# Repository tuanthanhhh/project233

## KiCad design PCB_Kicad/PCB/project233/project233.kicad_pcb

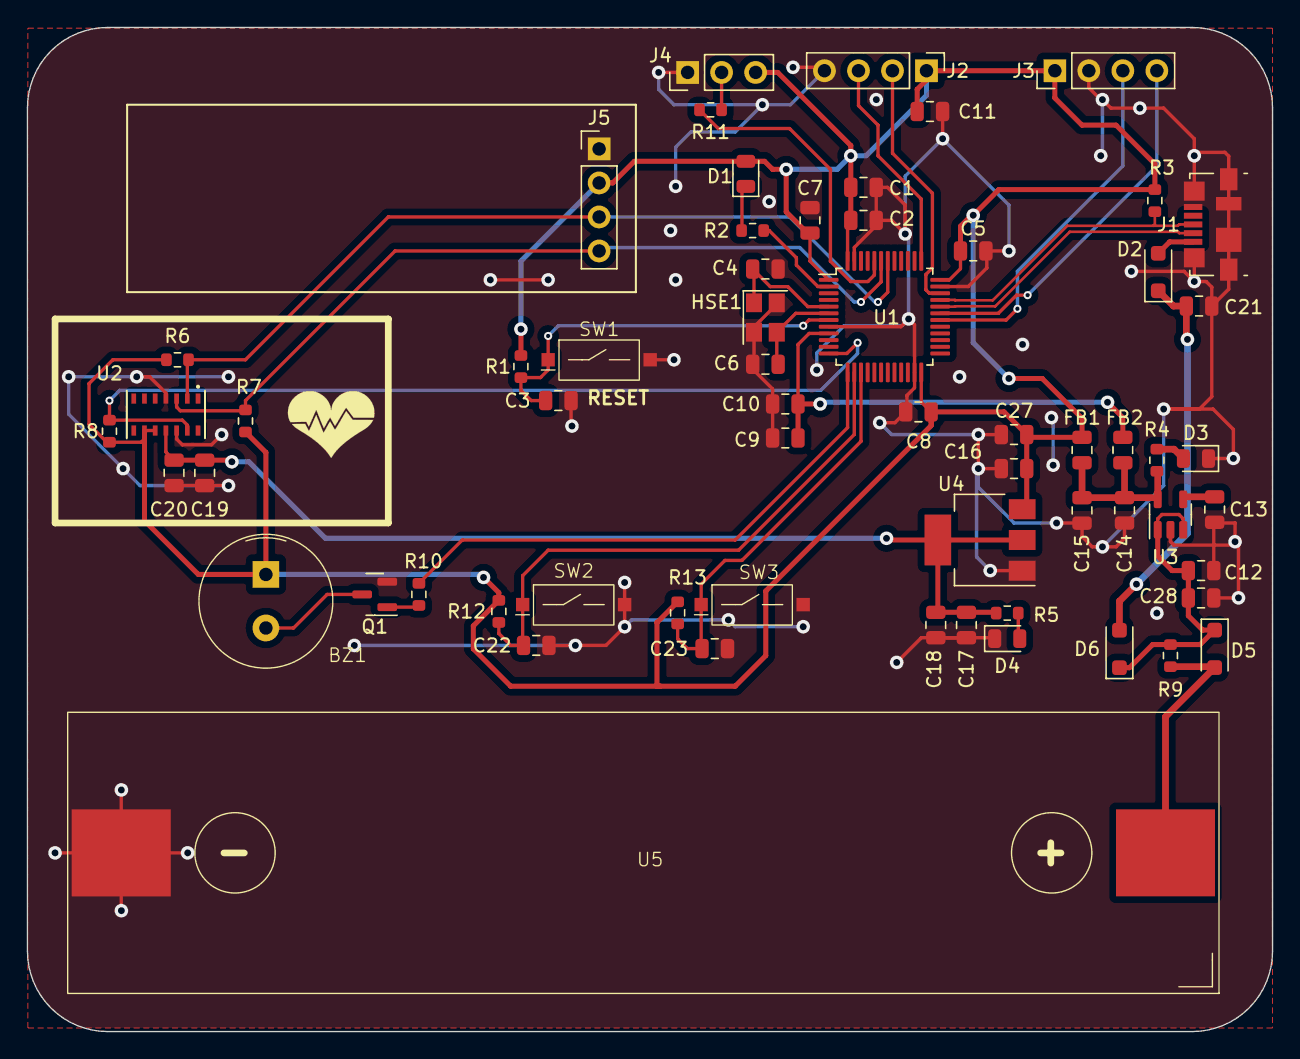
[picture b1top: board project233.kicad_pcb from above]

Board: 2 copper layers, 93.0 x 75.0 mm, 62 parts (0 on the bottom side), 33 nets.

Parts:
BZ1: Buzzer; Buzzer_9056_THT
C1: 4.7uF; C_0805_2012Metric
C2, C5, C7, C8, C9, C11, C13, C15, C16, C17, C21, C22, C23, C28: 100nF; C_0805_2012Metric
C3: 4.7nF; C_0805_2012Metric
C4, C6: 15pF; C_0805_2012Metric
C10: 1uF; C_0805_2012Metric
C12: 10uF/16V; C_0805_2012Metric
C14: 22uF/16V; C_0805_2012Metric
C18, C19, C27: 10uF; C_0805_2012Metric
C20: 100n; C_0805_2012Metric
D1: RED_LED; LED_0805_2012Metric
D2: B120-E3; D_SOD-123F
D3, D4: LED; LED_0805_2012Metric
D5, D6: 1N4007; D_SOD-123F
FB1, FB2: 0805; C_0805_2012Metric
HSE1: 8MHz; Crystal_SMD_3225-4Pin_3.2x2.5mm
J1: USB_B_Micro; USB_Micro-B_Molex_47346-0001
J2, J3, J5: Header_1x4; PinHeader_1x04_P2.54mm_Vertical
J4: Header_1x3; PinHeader_1x03_P2.54mm_Vertical
Q1: 2SC1815; SOT-23
R1, R11: 10k; R_0603_1608Metric
R2, R10: 150R; R_0603_1608Metric
R3: 4k7; R_0603_1608Metric
R4, R5, R9, R12, R13: 1k; R_0603_1608Metric
R6, R7, R8: 1K; R_0603_1608Metric
SW1: RESET; Button_3x6_SMD
SW2: BT1; Button_3x6_SMD
SW3: BT2; Button_3x6_SMD
U1: STM32F103C8T6; LQFP-48_7x7mm_P0.5mm
U2: MAX30102EFD_; 21-1048_F143A5&plus_1_MXM
U3: RT9193-33GB; SOT-23-5
U4: AMS1117-1.8; SOT-223-3_TabPin2
U5: Batt_Holder; Holder_18650_SMD

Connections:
+1V8: C17.1, C18.1, C19.1, C20.1, R5.1, U2.11 (VDD), U4.2 (VO)
+5V: C21.1, D2.1 (K), D6.2 (A)
/MCU/BOOT0: R11.2, U1.44 (BOOT0)
/MCU/BT_1: C22.1, R12.2, SW2.1, U1.14 (PA4)
/MCU/BT_2: C23.1, R13.2, SW3.1, U1.15 (PA5)
/MCU/BUZZER_EN: R10.2, U1.13 (PA3)
/MCU/DEBUG_LED: R2.1, U1.2 (PC13)
/MCU/HSE_IN: C4.1, HSE1.1, U1.5 (PD0)
/MCU/HSE_OUT: C6.1, HSE1.3, U1.6 (PD1)
/MCU/NRST: C3.1, R1.1, SW1.1, U1.7 (NRST)
/MCU/RX: J3.3, U1.30 (PA9)
/MCU/SWCLK: J2.3, U1.37 (PA14)
/MCU/SWDIO: J2.2, U1.34 (PA13)
/MCU/TX: J3.4, U1.31 (PA10)
/MCU/USB+: J1.3 (D+), R3.2, U1.33 (PA12)
/MCU/USB-: J1.2 (D-), U1.32 (PA11)
GND: C1.2, C2.2, C3.2, C4.2, C5.2, C6.2, C7.2, C8.2, C9.2, C10.2, C11.2, C12.2, C13.2, C14.2, C15.2, C16.2, C17.2, C18.2, C19.2, C20.2, C21.2, C22.2, C23.2, C27.2, C28.2, D3.1 (K), D4.1 (K), HSE1.2, HSE1.4, J1.5 (GND), J1.6 (Shield), J2.4, J3.2, J4.1, J5.1, Q1.2 (E), SW1.2, SW2.2, SW3.2, U1.8 (VSSA), U1.23 (VSS), U1.35 (VSS), U1.47 (VSS), U2.4 (PGND), U2.12 (GND), U3.2 (GND), U4.1 (GND), U5.2 (-)
unnamed: BZ1.2 (+), Q1.3 (C)
unnamed: D1.1 (K), R2.2
unnamed: D2.2 (A), J1.1 (VBUS)
unnamed: D3.2 (A), R4.2
unnamed: D4.2 (A), R5.2
unnamed: D5.2 (A), R9.2, U5.1 (+)
unnamed: C12.1, C28.1, D5.1 (K), D6.1 (K), R9.1, U3.1 (VIN), U3.3 (EN)
unnamed: J4.2, R11.1
unnamed: Q1.1 (B), R10.1
unnamed: C13.1, U3.4 (BP)
unnamed: C14.1, C15.1, FB1.2, FB2.2, R4.1, U3.5 (VOUT)
SCL: J5.3, R6.2, U1.42 (PB6), U2.2 (SCL)
SDA: J5.4, R7.2, U1.43 (PB7), U2.3 (SDA)
VCC: BZ1.1 (-), C1.1, C2.1, C5.1, C7.1, C8.1, C11.1, C16.1, C27.1, D1.2 (A), FB1.1, J2.1, J3.1, J4.3, J5.2, R1.2, R3.1, R6.1, R7.1, R8.2, R12.1, R13.1, U1.1 (VBAT), U1.24 (VDD), U1.36 (VDD), U1.48 (VDD), U2.9 (VLED+), U2.10 (VLED+), U4.3 (VI)
VDDA: C9.1, C10.1, FB2.1, U1.9 (VDDA)
~INT: R8.1, U1.12 (PA2), U2.13 (~INT)

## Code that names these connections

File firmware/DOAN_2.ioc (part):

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Mcu.Name=STM32F103C(8-B)Tx
Mcu.Package=LQFP48
Mcu.UserName=STM32F103C8Tx
PA10.Mode=Asynchronous
PA10.Signal=USART1_RX
PA11.Mode=Device
PA11.Signal=USB_DM
PA12.Mode=Device
PA12.Signal=USB_DP
PA13.Mode=Serial_Wire
PA13.Signal=SYS_JTMS-SWDIO
PA14.Mode=Serial_Wire
PA14.Signal=SYS_JTCK-SWCLK
PA2.GPIOParameters=GPIO_PuPd,GPIO_Label,GPIO_ModeDefaultEXTI
PA2.GPIO_Label=INT
PA2.GPIO_ModeDefaultEXTI=GPIO_MODE_IT_FALLING
PA2.GPIO_PuPd=GPIO_NOPULL
PA2.Signal=GPXTI2
PA3.GPIOParameters=GPIO_Label
PA3.GPIO_Label=BUZZER
PA3.Signal=S_TIM2_CH4
PA4.GPIOParameters=GPIO_PuPd,GPIO_Mode
PA4.GPIO_Mode=GPIO_MODE_INPUT
PA4.GPIO_PuPd=GPIO_PULLUP
PA4.Signal=GPIO_Input
PA5.GPIOParameters=GPIO_PuPd
PA5.GPIO_PuPd=GPIO_PULLUP
PA5.Signal=GPIO_Input
PA9.Mode=Asynchronous
PA9.Signal=USART1_TX
PB6.Mode=I2C
PB6.Signal=I2C1_SCL
PB7.Mode=I2C
PB7.Signal=I2C1_SDA
PC13-TAMPER-RTC.GPIOParameters=GPIO_Label
PC13-TAMPER-RTC.GPIO_Label=TEST
PC13-TAMPER-RTC.Signal=GPIO_Output
PD0-OSC_IN.Mode=HSE-External-Oscillator
PD0-OSC_IN.Signal=RCC_OSC_IN
PD1-OSC_OUT.Mode=HSE-External-Oscillator
PD1-OSC_OUT.Signal=RCC_OSC_OUT
RCC.SYSCLKFreq_VALUE=48000000
RCC.SYSCLKSource=RCC_SYSCLKSOURCE_PLLCLK
board=custom

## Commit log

2024-06-06 create project
2024-06-21 update hard ware, firmware, datasheet
2024-06-22 update 22/06/2024
2024-06-24 update kicad PCB
2024-06-25 update PCB
2024-06-25 update 3D Lib
2024-06-28 updated pcb
2024-07-02 complete PCB design
2024-07-03 export gerber file
2024-07-04 add oled and max30102 function
2024-07-04 add docs firmware
2024-07-05 export Gerber
2024-07-05 add Gerber.rar
2024-07-05 add Gerber.zip
2024-07-07 add image docs
2024-07-12 update firmware
2024-07-14 move firmware file and note docs
2024-07-14 update docs
2024-07-16 fix schematic and PCB
2024-07-16 add image files, change layout schematic and update firmware
2024-07-18 update 18/07
2024-07-23 add image and update firmware
2024-08-28 update 28/08
2024-08-28 add firmware_V2 and fix bug
2024-08-29 fixbug and add several function
2024-09-18 add esp32 and update STM32
2024-09-26 final project
